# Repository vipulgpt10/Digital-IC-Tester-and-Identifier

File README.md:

# Digital-IC-Tester-and-Identifier

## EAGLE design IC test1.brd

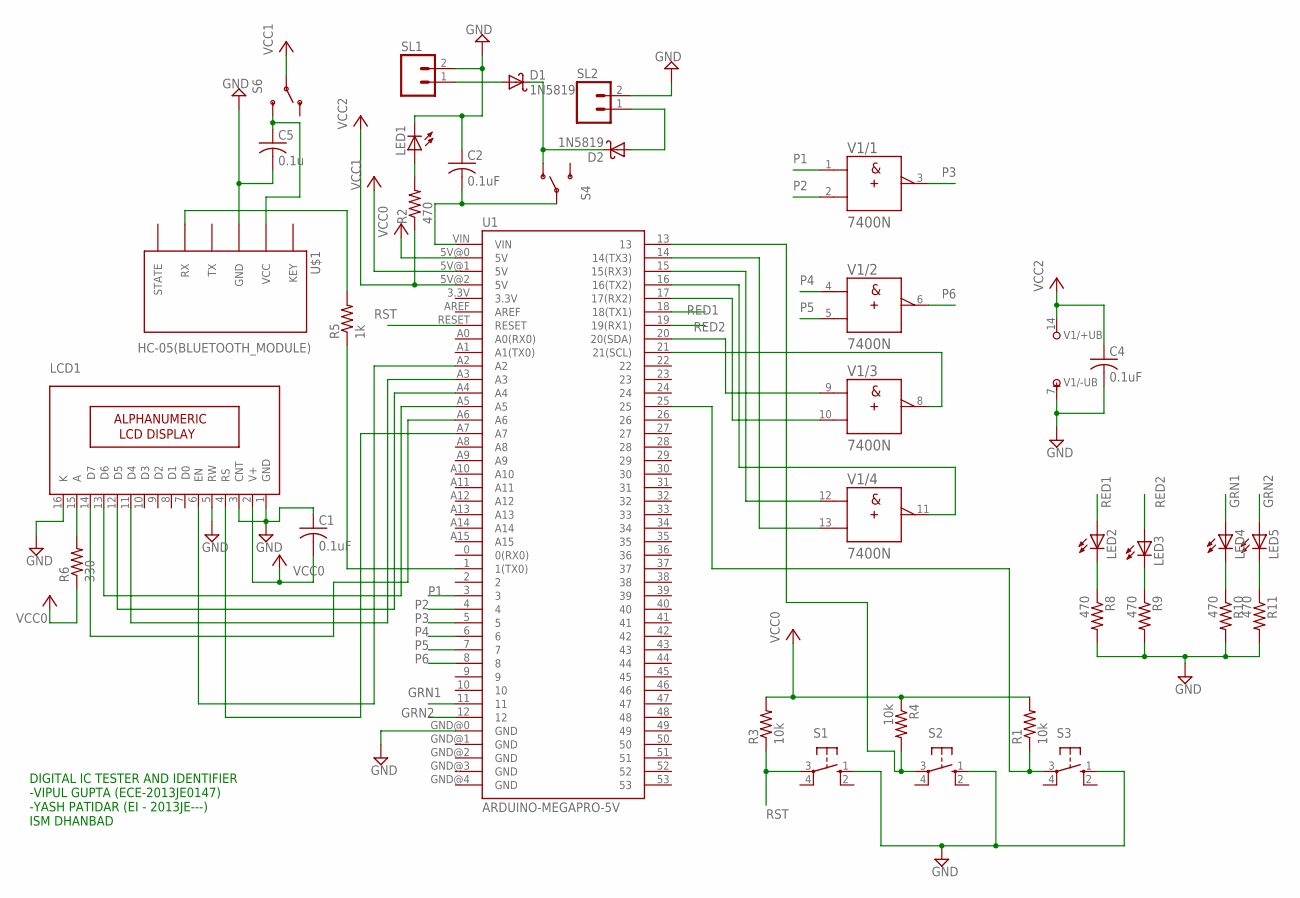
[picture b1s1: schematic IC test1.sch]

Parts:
C1, C2, C4: 0.1uF; C025-024X044
C5: 0.1u; C025-024X044
D1, D2: 1N5819; DO41-10
LCD1: 16X2LCD; 16X2_LCD
LED1, LED2, LED3, LED4, LED5: LED5MM
R1, R3, R4: 10k; 0204/7
R2, R8, R9, R10, R11: 470; 0204/7
R5: 1k; 0204/7
R6: 330; 0204/7
S1, S2, S3: 40-XX; B3F-40XX
S4, S6: SWITCH-SPDTPTH; SWITCH-SPDT
SL1, SL2: M02; 02P
U1: ARDUINO-MEGAPRO-5V; ARDUINO_MEGA-PRO-5V
U$1: HC-05(BLUETOOTH_MODULE); HC-05
V1: 7400N; DIL14

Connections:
GND: C1.1, C2.1, C4.2, C5.2, LCD1.1 (GND), LCD1.3 (CNT), LCD1.5 (RW), LCD1.16 (K), LED1.K (C), R8.2, R9.2, R10.2, R11.2, S1.1 (S), S2.1 (S), S3.1 (S), SL1.2, SL2.2, U1.GND@0 (GND), U$1.GND, V1.7 (-UB)
GRN1: LED4.A, U1.11
GRN2: LED5.A, U1.12
unnamed: LCD1.15 (A), R6.2
unnamed: R5.2, U$1.RX
unnamed: LCD1.4 (RS), U1.A7
unnamed: LCD1.6 (EN), U1.A2
unnamed: LCD1.11 (D4), U1.A3
unnamed: LCD1.12 (D5), U1.A4
unnamed: LCD1.13 (D6), U1.A5
unnamed: LCD1.14 (D7), U1.A6
unnamed: D1.C, D2.C, S4.1 (O)
unnamed: D2.A, SL2.1
unnamed: C2.2, S4.2, U1.VIN
unnamed: D1.A, SL1.1
unnamed: C5.1, S6.3 (S), U$1.VCC
unnamed: U1.14 (14(TX3)), V1.13 (B)
unnamed: R4.2, S2.3, U1.13
unnamed: R1.1, S3.3, U1.25
unnamed: U1.15 (15(RX3)), V1.12 (A)
unnamed: LED1.A, R2.2
unnamed: U1.16 (16(TX2)), V1.11 (Y)
unnamed: U1.17 (17(RX2)), V1.10 (B)
unnamed: U1.20 (20(SDA)), V1.9 (A)
unnamed: U1.21 (21(SCL)), V1.8 (Y)
unnamed: LED2.K (C), R8.1
unnamed: LED3.K (C), R9.1
unnamed: LED4.K (C), R10.1
unnamed: LED5.K (C), R11.1
unnamed: R5.1, U1.1 (1(TX0))
P1: U1.3, V1.1 (A)
P2: U1.4, V1.2 (B)
P3: U1.5, V1.3 (Y)
P4: U1.6, V1.4 (A)
P5: U1.7, V1.5 (B)
P6: U1.8, V1.6 (Y)
RED1: LED2.A, U1.18 (18(TX1))
RED2: LED3.A, U1.19 (19(RX1))
RST: R3.1, S1.3, U1.RESET
VCC0: C1.2, LCD1.2 (V+), R1.2, R3.2, R4.1, R6.1, U1.5V@0 (5V)
VCC3: R2.1, S6.2, U1.5V@2 (5V)
VCC4: C4.1, U1.5V@1 (5V), V1.14 (+UB)

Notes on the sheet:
DIGITAL IC TESTER AND IDENTIFIER -VIPUL GUPTA (ECE-2013JE0147) -YASH PATIDAR (EI - 2013JE---) ISM DHANBAD

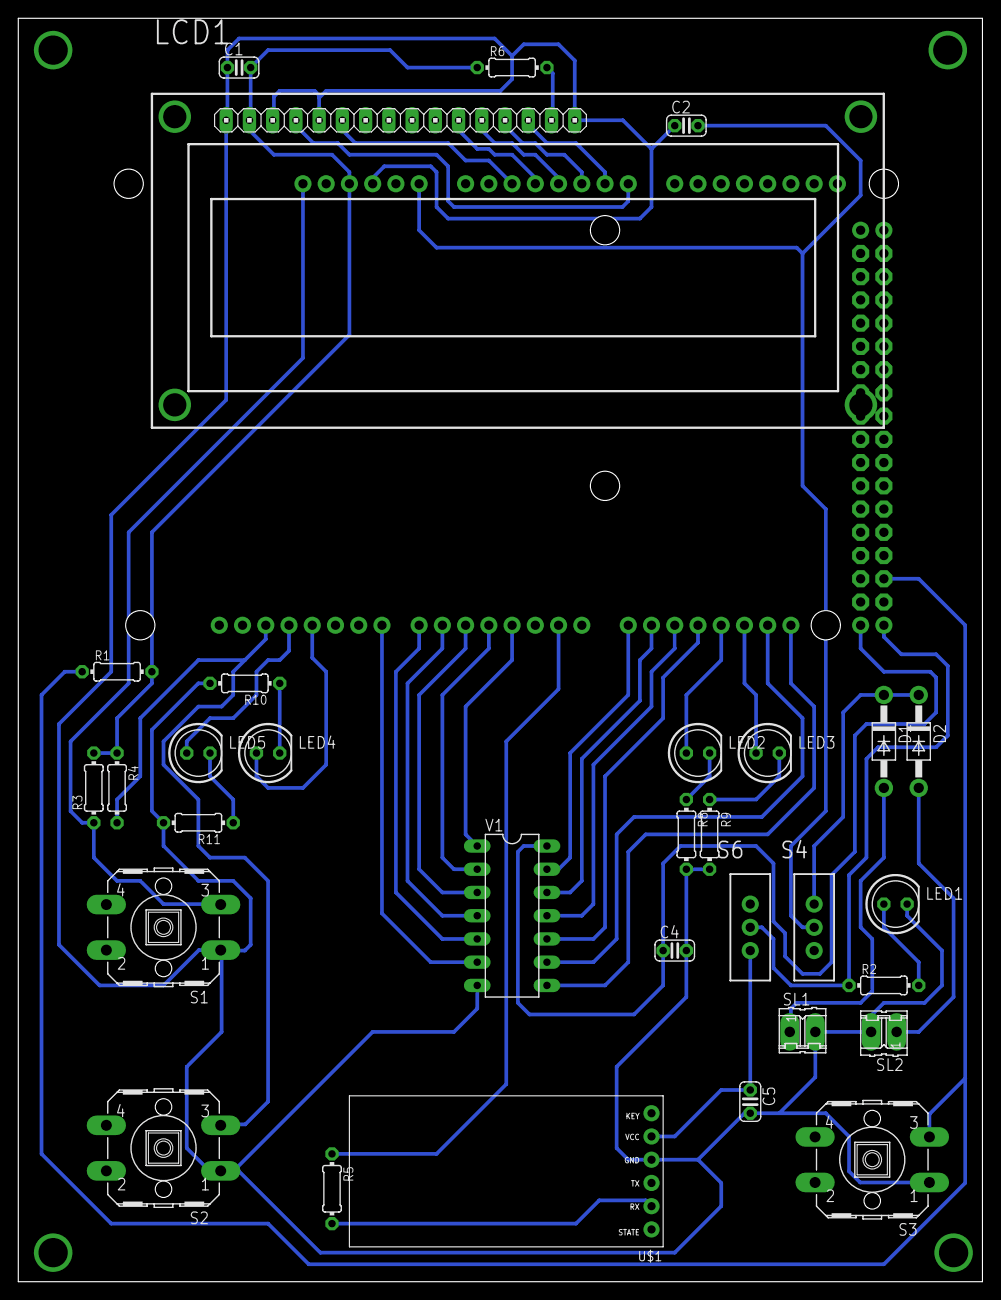
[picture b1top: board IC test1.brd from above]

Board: 2 copper layers, 105.4 x 138.1 mm, 32 parts (1 on the bottom side), 42 nets.

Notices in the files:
parts and their libraries:
SparkFun-Boards: Licensing: Creative Commons ShareAlike 4.0 International - https://creativecommons.org/licenses/by-sa/4.0
